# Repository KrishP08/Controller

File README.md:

# Controller
This is xbox layout controller that have hall effect joystick,hall effect triggers,and two rumble motor,a,b,x,y,up,down,left,right,lb,rb,start,home,select and we use gp2040-ce firmware with pi pico W
# PCB 

# CAD

# Firmware
In this we use gp2040-ce Firmware so for latest version go to https://gp2040-ce.info/ and select Pico w board firmware and download it 
# How to use 
First place and solder all the part
flast the firmware to pico 
then add pico to pcb 
To use web-based configuration aplication which can be started by holding HOME when plugging your controller into a PC or by holding HOME + LB + RB for five seconds while the controller is plugged in. Then access http://192.168.7.1 in a web browser to begin configuration.
Play

# why I made the project
I want to try make i my own controller that i can play on any consol without lossing any consols features 

# BOM

| No | Product Name                             | Qty | Price / Piece (₹) |     Total (₹) | Total (USD) | Notes                 | Link                                                                                          |
| -: | ---------------------------------------- | --: | ----------------: | ------------: | ----------: | --------------------- | --------------------------------------------------------------------------------------------- |
|  1 | Tactile Push Button Switch 6×6×5         |  14 |              2.00 |         28.00 |        0.02 | —                     | [Link](https://robu.in/product/6x6x5-tactile-push-button-switch/)                             |
|  2 | Raspberry Pi Pico W                      |   1 |            614.00 |        614.00 |        6.81 | —                     | [Link](https://robu.in/product/raspberry-pi-pico-w/)                                          |
|  3 | 2PCS Hall Effect Sensor Joystick         |   1 |            847.00 |        847.00 |        9.40 | —                     | [Link](https://www.amazon.in/dp/B0CNWYWCYN)                                                   |
|  4 | CJMCU-4051 (74HC4051) Analog Multiplexer |   1 |             76.00 |         76.00 |        0.84 | —                     | [Link](https://robu.in/product/cjmcu-4051-74hc4051-8-channel-analog-multiplexer/)             |
|  5 | AO3400A MOSFET (30V, 5.2A)               |   2 |              6.00 |         12.00 |        0.13 | —                     | [Link](https://robu.in/product/ao3400a-mosfet/)                                               |
|  6 | 1N4148W Diode (75V, 150mA, SOD)          |   2 |              1.43 |          2.86 |        0.03 | —                     | [Link](https://robu.in/product/1n4148w-slkor-75v-1v-4ns-150ma-sod-123-switching-diodes-rohs/) |
|  7 | 10kΩ 0.5W Metal Film Resistor            |   2 |              0.98 |          1.96 |        0.02 | —                     | [Link](https://robu.in/product/10k-ohm-0-5w-metal-film-resistor-pack-of-50/)                  |
|  8 | Neodymium Magnet 4mm × 2mm (2 pcs)       |   1 |             11.80 |         11.80 |        0.13 | —                     | [Link](https://roboticsdna.in/product/4mm-x-2mm-neodymium-disc-strong-magnet-2-piece/)        |
|  9 | MPU-6050 3-Axis Accelerometer            |   1 |            173.00 |        173.00 |        1.92 | —                     | [Link](https://robu.in/product/mpu-6050-gyro-sensor-2-accelerometer/)                         |
| 10 | Honeywell Hall Effect Sensor (SS49E)     |   2 |            106.00 |        212.00 |        2.35 | —                     | [Link](https://robu.in/product/honeywell-board-mount-hall-effect-magnetic-sensors-ss49e/)     |
| 11 | 4000 RPM 5V DC Vibration Motor           |   2 |             29.00 |        137.00 |        1.52 | 58 + 79 Delivery      | [Link](https://electronicspices.com/product/4000-rpm-5v-dc-vibration-rumble-motor)            |
| 12 | PCB (JLCPCB)                             |   1 |           1934.74 |       1934.74 |       21.06 | 7.20 + 13.86 Delivery | [Link](https://jlcpcb.com/)                                                                   |
| 13 | 3D Printed Enclosure                     |   1 |           1995.00 |       1995.00 |       22.13 | —                     | [Link](https://robu.in/product/3d-printing-service/)                                          |
| 14 | KFC-A06W1-7.0-Tact Switch with Bracket  |   2 |           3 |       6 |       0.07 | —                     | [Link](https://robu.in/product/kfc-a06w1-7-0-tact-switch-with-bracket-2-pin6x6x7/?gad_source=1&gad_campaignid=17427802703&gbraid=0AAAAADvLFWcf0A3fY80VS7iF_2pv895su&gclid=Cj0KCQiAp-zLBhDkARIsABcYc6t9Cs5FOjAbGKIwALZDaRnHzBKde80b59d5eUpMGOVjkTpeyJFkiuwaAphZEALw_wcB)                                                                   |
|    | **Total**                                |     |                   | **₹ 6051.36** | **$ 66.72** |                       |                                                                                               |

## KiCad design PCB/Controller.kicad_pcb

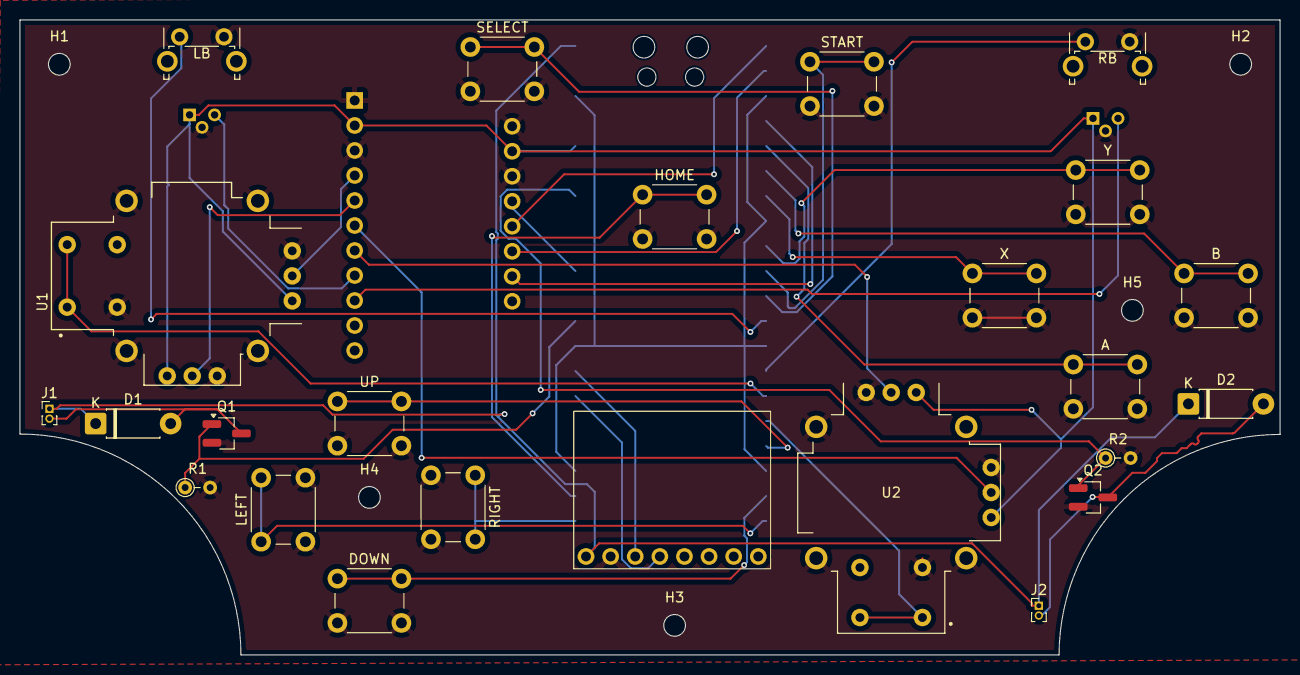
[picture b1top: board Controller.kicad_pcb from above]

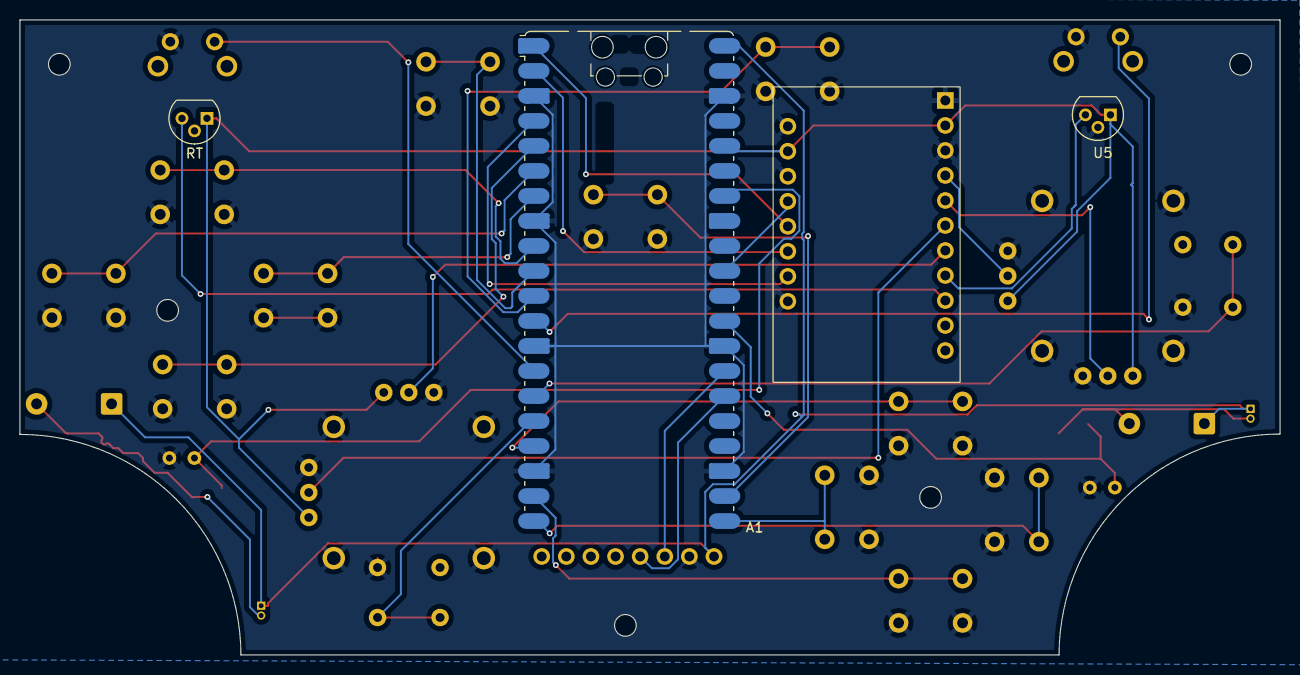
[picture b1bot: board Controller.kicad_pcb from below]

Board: 2 copper layers, 128.0 x 64.5 mm, 33 parts (4 on the bottom side), 34 nets.

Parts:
A: SW_Push; SW_PUSH_6mm
A1: RaspberryPi_Pico_W; RaspberryPi_Pico_W_SMD_HandSolder
B: SW_Push; SW_PUSH_6mm
D1, D2: D; D_DO-41_SOD81_P7.62mm_Horizontal
DOWN: SW_Push; SW_PUSH_6mm
H1: MH_2.2mm; MountingHole_2.2mm_M2_DIN965
H2, H3, H4, H5: MountingHole_2.2mm_M2_DIN965
HOME: SW_Push; SW_PUSH_6mm
J1, J2: Conn_01x02_Pin; PinHeader_1x02_P1.00mm_Vertical
LB: SW_Push; SW_Tactile_SPST_Angled_PTS645Vx39-2LFS
LEFT: SW_Push; SW_PUSH_6mm
MPU1: MPU6050; mpu6050
Q1, Q2: Q_NMOS_GSD; SOT-23_Handsoldering
R1, R2: R; R_Axial_DIN0204_L3.6mm_D1.6mm_P2.54mm_Vertical
RB: SW_Push; SW_Tactile_SPST_Angled_PTS645Vx39-2LFS
RIGHT: SW_Push; SW_PUSH_6mm
RT: TO-92
SELECT: SW_Push; SW_PUSH_6mm
START: SW_Push; SW_PUSH_6mm
U1, U2: COM-09032; XDCR_COM-09032
U3: 74HC4051
U5: TO-92
UP: SW_Push; SW_PUSH_6mm
X: SW_Push; SW_PUSH_6mm
Y: SW_Push; SW_PUSH_6mm

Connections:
+3.3V: A1.36 (3V3), RT.1 (VCC), U1.H1 (H+), U1.V1 (V+), U2.H1 (H+), U2.V1 (V+), U3.2 (VCC), U5.1 (VCC)
+5V: A1.40 (VBUS), D1.1 (K), D2.1 (K), J1.1, J2.1, MPU1.1 (VCC)
A: A.1, A1.5 (GPIO3)
B: A1.6 (GPIO4), B.1
DOWN: A1.19 (GPIO14), DOWN.1
GND: A.2, A1.3 (GND), A1.8 (GND), A1.13 (GND), A1.18 (GND), A1.23 (GND), A1.28 (GND), A1.38 (GND), B.2, DOWN.2, HOME.2, LB.2, LEFT.2, MPU1.2 (GND), Q1.2 (S), Q2.2 (S), R1.2, R2.2, RB.2, RIGHT.2, RT.2 (GND), SELECT.2, START.2, U1.B2A (SEL-), U1.H3 (H-), U1.S1 (SHIELD), U1.S2 (SHIELD), U1.S3 (SHIELD), U1.S4 (SHIELD), U1.V3 (V-), U2.B2A (SEL-), U2.H3 (H-), U2.S1 (SHIELD), U2.S2 (SHIELD), U2.S3 (SHIELD), U2.S4 (SHIELD), U2.V3 (V-), U3.1 (VEE), U3.3 (GND), U3.16 (E), U5.2 (GND), UP.2, X.2, Y.2
HOME: A1.22 (GPIO17), HOME.1
L3: A1.15 (GPIO11), U1.B1A (SEL+), U1.B1B
LB: A1.12 (GPIO9), LB.1
LEFT: A1.20 (GPIO15), LEFT.1
LM: A1.29 (GPIO22), Q1.1 (G), R1.1
LT: U3.8 (Y4), U5.3 (OUT)
unnamed: D1.2 (A), J1.2, Q1.3 (D)
unnamed: D2.2 (A), J2.2, Q2.3 (D)
R3: A1.16 (GPIO12), U2.B1A (SEL+), U2.B1B
RB: A1.14 (GPIO10), RB.1
RIGHT: A1.21 (GPIO16), RIGHT.1
RM: A1.34 (GPIO28_ADC2), Q2.1 (G), R2.1
RT: RT.3 (OUT), U3.9 (Y5)
S0: A1.1 (GPIO0), U3.13 (S0)
S1: A1.2 (GPIO1), U3.14 (S1)
S2: A1.4 (GPIO2), U3.15 (S2)
SCL: A1.27 (GPIO21), MPU1.3 (SCL)
SDA: A1.26 (GPIO20), MPU1.4 (SDA)
SELECT: A1.11 (GPIO8), SELECT.1
START: A1.10 (GPIO7), START.1
UP: A1.17 (GPIO13), UP.1
X: A1.7 (GPIO5), X.1
Y: A1.9 (GPIO6), Y.1
Y0: U1.H2 (H), U3.4 (Y0)
Y1: U1.V2 (V), U3.5 (Y1)
Y2: U2.V2 (V), U3.6 (Y2)
Y3: U2.H2 (H), U3.7 (Y3)
Z: A1.31 (GPIO26_ADC0), U3.12 (Z)

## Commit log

2026-01-29 Create a
2026-01-29 Create Images
2026-02-21 Create f
